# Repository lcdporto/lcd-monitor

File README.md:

# LCD Monitor

Project to create a Facilities Monitor and Access Control System  for a shared space.

As our work space is shared by several people, we want to have the greatest flexibility and at the same time security and responsibility, access control is a challenge that we have long tried to solve.

We resolved to cannibalize the current alarm and create a new one whose programming is much more flexible.

---

The progress of this project can be tracked (in Portuguese) in a [blog post](https://blog.lcdporto.org/project-lcd-monitor/) at our blog.

---

## Brief description

The console will be run by a Arduino and an API running on a server, the Arduino will handle all the sensors, keypad and buzzers independently.

The API (probably using Django REST) to communicate events and receive instructions.

After receiving new programming the API will pass it to the Arduino via  ethernet.

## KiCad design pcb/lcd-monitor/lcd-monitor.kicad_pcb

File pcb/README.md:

# LCD Monitor - PCB

## Requirements

* Pass 12v to the sensors and feed return signal throught optocouplers to the Arduino
* Signaling using LEDs (armed/clear/alarm/zones)
* PCB headers to the [keypad](16-Key-4-x-4-Membrane-Keypad.jpg)  
* PCB headers to hold Arduino Nano or, build an Arduino on the board
* Feed 5v to the Arduino
* PCB headers to [ethernet module](Mini-ENC28J60-Ethernet-LAN-Network-Module-AVR-SPI-PIC-STM32-LPC.jpg)
* Charging circuit to a 12v battery
* Anti-tampering push button on the board

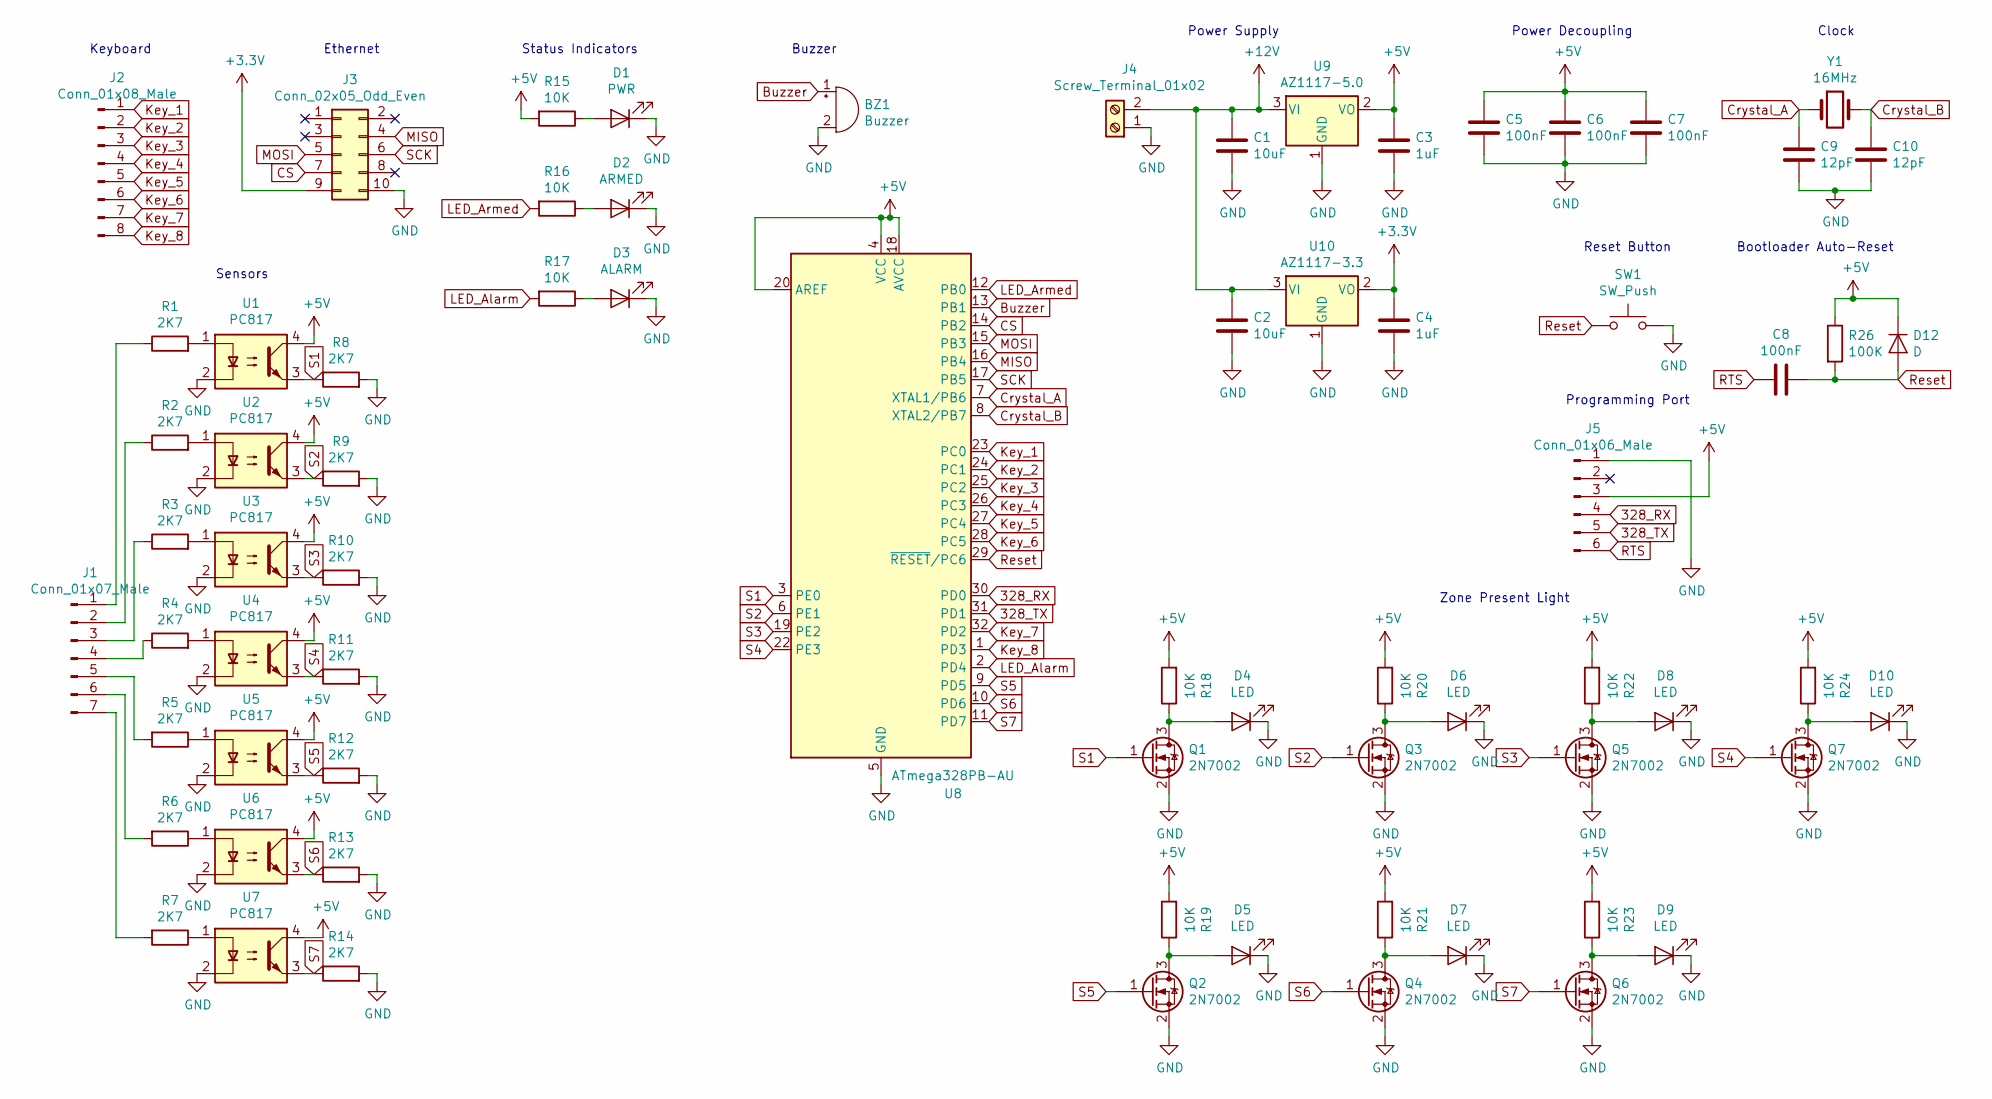
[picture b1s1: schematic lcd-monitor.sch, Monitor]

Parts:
BZ1: Buzzer; Buzzer_12x9.5RM7.6
C1, C2: 10uF; C_0805_2012Metric
C3, C4: 1uF; C_0805_2012Metric
C5, C6, C7, C8: 100nF; C_0805_2012Metric
C9, C10: 12pF; C_0805_2012Metric
D1: PWR; LED_0805_2012Metric
D2: ARMED; LED_0805_2012Metric
D3: ALARM; LED_0805_2012Metric
D4, D5, D6, D7, D8, D9, D10: LED; LED_0805_2012Metric
D12: D; D_0805_2012Metric
J1: Conn_01x07_Male; PinHeader_1x07_P2.54mm_Vertical
J2: Conn_01x08_Male; PinHeader_1x08_P2.54mm_Vertical
J3: Conn_02x05_Odd_Even; PinSocket_2x05_P2.54mm_Vertical
J4: Screw_Terminal_01x02; TerminalBlock_Altech_AK300-2_P5.00mm
J5: Conn_01x06_Male; PinHeader_1x06_P2.54mm_Vertical
Q1, Q2, Q3, Q4, Q5, Q6, Q7: 2N7002; SOT-23
R1, R2, R3, R4, R5, R6, R7, R8, R9, R10, R11, R12, R13, R14: 2K7; R_0805_2012Metric
R15, R16, R17, R18, R19, R20, R21, R22, R23, R24: 10K; R_0805_2012Metric
R26: 100K; R_0805_2012Metric
SW1: SW_Push; SW_SPST_FSMSM
U1, U2, U3, U4, U5, U6, U7: PC817; DIP-4_W7.62mm
U8: ATmega328PB-AU; TQFP-32_7x7mm_P0.8mm
U9: AZ1117-5.0; SOT-223
U10: AZ1117-3.3; SOT-223
Y1: 16MHz; Crystal_SMD_3225-4Pin_3.2x2.5mm

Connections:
328_RX: J5.4, U8.30 (PD0)
328_TX: J5.5, U8.31 (PD1)
+3V3: C4.1, J3.9, U10.2 (VO)
+5V: C3.1, C5.1, C6.1, C7.1, D12.1 (K), J5.3, R15.2, R18.2, R19.2, R20.2, R21.2, R22.2, R23.2, R24.2, R26.1, U1.4, U2.4, U3.4, U4.4, U5.4, U6.4, U7.4, U8.4 (VCC), U8.18 (AVCC), U8.20 (AREF), U9.2 (VO); also elsewhere on the board
+12V: C1.1, C2.1, J4.2, U9.3 (VI), U10.3 (VI)
Buzzer: BZ1.1 (-), U8.13 (PB1)
CS: J3.7, U8.14 (PB2)
Crystal_A: C9.1, U8.7 (XTAL1/PB6), Y1.1
Crystal_B: C10.1, U8.8 (XTAL2/PB7), Y1.2
GND: BZ1.2 (+), C1.2, C2.2, C3.2, C4.2, C5.2, C6.2, C7.2, C9.2, C10.2, D1.1 (K), D2.1 (K), D3.1 (K), D4.1 (K), D5.1 (K), D6.1 (K), D7.1 (K), D8.1 (K), D9.1 (K), D10.1 (K), J3.10, J4.1, J5.1, Q1.2 (S), Q2.2 (S), Q3.2 (S), Q4.2 (S), Q5.2 (S), Q6.2 (S), Q7.2 (S), R8.2, R9.2, R10.2, R11.2, R12.2, R13.2, R14.2, SW1.2, U1.2, U2.2, U3.2, U4.2, U5.2, U6.2, U7.2, U8.5 (GND), U8.21 (GND), U9.1 (GND), U10.1 (GND); also elsewhere on the board
Key_1: J2.1, U8.23 (PC0)
Key_2: J2.2, U8.24 (PC1)
Key_3: J2.3, U8.25 (PC2)
Key_4: J2.4, U8.26 (PC3)
Key_5: J2.5, U8.27 (PC4)
Key_6: J2.6, U8.28 (PC5)
Key_7: J2.7, U8.32 (PD2)
Key_8: J2.8, U8.1 (PD3)
LED_Alarm: R17.2, U8.2 (PD4)
LED_Armed: R16.2, U8.12 (PB0)
MISO: J3.4, U8.16 (PB4)
MOSI: J3.5, U8.15 (PB3)
unnamed: D1.2 (A), R15.1
unnamed: D2.2 (A), R16.1
unnamed: D3.2 (A), R17.1
unnamed: D4.2 (A), Q1.3 (D), R18.1
unnamed: D5.2 (A), Q2.3 (D), R19.1
unnamed: D6.2 (A), Q3.3 (D), R20.1
unnamed: D7.2 (A), Q4.3 (D), R21.1
unnamed: D8.2 (A), Q5.3 (D), R22.1
unnamed: D9.2 (A), Q6.3 (D), R23.1
unnamed: D10.2 (A), Q7.3 (D), R24.1
unnamed: J1.1, R1.1
unnamed: J1.2, R2.1
unnamed: J1.3, R3.1
unnamed: J1.4, R4.1
unnamed: J1.5, R5.2
unnamed: J1.6, R6.2
unnamed: J1.7, R7.2
unnamed: R1.2, U1.1
unnamed: R2.2, U2.1
unnamed: R3.2, U3.1
unnamed: R4.2, U4.1
unnamed: R5.1, U5.1
unnamed: R6.1, U6.1
unnamed: R7.1, U7.1
RTS: C8.2, J5.6
Reset: C8.1, D12.2 (A), R26.2, SW1.1, U8.29 (~RESET~/PC6)
S1: Q1.1 (G), R8.1, U1.3, U8.3 (PE0)
S3: Q5.1 (G), R10.1, U3.3, U8.19 (PE2)
S5: Q2.1 (G), R12.1, U5.3, U8.9 (PD5)
SCK: J3.6, U8.17 (PB5)

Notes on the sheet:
Clock
Power Decoupling
Bootloader Auto-Reset
Power Supply
Reset Button
Programming Port
Keyboard
Ethernet
Status Indicators
Buzzer
Sensors
Zone Present Light

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
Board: 2 copper layers, 74 parts (0 on the bottom side), 57 nets, no tracks yet.

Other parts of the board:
D11: LED; LED_0805_2012Metric
Q8: 2N7002; SOT-23
R25: 10K; R_0805_2012Metric

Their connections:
+5V: R25.2; also elsewhere on the board
GND: D11.1, Q8.2; also elsewhere on the board
unnamed: D11.2, Q8.3, R25.1

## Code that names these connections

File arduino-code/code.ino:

/*
 *
 *  Uses https://playground.arduino.cc/code/keypad
 *
 *
 */

#include "Arduino.h"
#include <EEPROM.h>
#include <Keypad.h>
#include <elapsedMillis.h>
#include "loadConfig.cpp"
/******************
 * PIN asignments
 */

// used by the keypad
byte rowPins[] = {A7,A6,A5,A4};
byte colPins[] = {A3,A2,A1,A0};

// active zones
const byte zones[2] = { 2, 3 };

// the LEDs
const byte LED_ALARM = 9;
const byte LED_ARMED = 13;

// the buzz
const byte Buzzer = 12;

// External alarm
const byte E_ALARM = 11;

/*
 * end PIN assigments
 *********************/


// struct with configuration to be stored on EEPROM
struct confSettings{
  bool zoneType[6];
  byte daferTime;
};

confSettings conf;

/* starting keypad */
// @TODO should this go into the function that andles the keypad
const char keys[4][4] = {
  {'1','2','3','A'},
  {'4','5','6','B'},
  {'7','8','9','C'},
  {'*','0','#','D'}
};
Keypad keypad = Keypad( makeKeymap(keys), rowPins, colPins, 4, 4 );

// Sound Codes
const byte sndStart=1;
const byte sndCancel=2;
const byte sndKeyPress=3;


/* zoneType: 0 = Instant Alarm; 1 = Deferred Alarm ); */
#define INSTANT_ALARM  1
#define DEFERRED_ALARM 0
bool zoneType[2] = {
  0,
  0
};

/* deferTime, time in seconds before a Deferred Alarm goes on */
byte deferTime = 15;

/* deferredAlarmState: 0 = no activity; 1 = in Deferred Alarm countdown */
bool deferredAlarmState = 0;
elapsedMillis deferredAlarmStart;

/* onAlarm: full blown Alarm in progress */
bool onAlarm = 0;
bool inInput=false;
bool isArmed=false;



int keyTone = 900;
int keyToneDuration = 50;
// =========================================================================88|

void setup() {

  // read EEPROM
  loadConfig();

  for ( int i = 0; i < sizeof(zones) - 1; i++ ) {
    pinMode(i,INPUT);
  }
  pinMode(LED_ALARM, OUTPUT); digitalWrite(LED_ALARM, HIGH);
  pinMode(LED_ARMED, OUTPUT); digitalWrite(LED_ARMED, HIGH);

  sound(sndStart);
  isArmed=true;
  Serial.begin(9600);
  delay(200);
}


/**
 * Da loop
 *
 * Faking multitasking, call all functions has fas as possible
 *
 */
void loop() {

  heartBeat();
  readZones();
  readKeypad();

  ledKeeper();
  soundKeeper();


}

// =========================================================================88|





//


/**
 * void hearBeat()
 *
 * give visual feedback that the software is running by temporarely inverting
 * the status of LED_ARMED
 */
#define HEART_BEAT_SLEEP 1000
#define HEART_BEAT_DURATION 50  // must be lower than HEART_BEAT_SLEEP
void heartBeat()
{
  static elapsedMillis timeElapsed;
  static bool onBeat = false; // if a heartbeat is currently ocorring

  if ( ( onBeat && timeElapsed > HEART_BEAT_DURATION ) || ( timeElapsed > HEART_BEAT_SLEEP ) )
  {
    onBeat = !onBeat;
    digitalWrite( LED_ARMED, !digitalRead( LED_ARMED ) );
    timeElapsed = 0;
  }

}


/* Read All Zones and trigger Alarm Events */
void readZones() {
  for ( int zone = 0; zone < sizeof(zones); zone++ ) {

    if( ( !digitalRead(zones[zone]) ) && isArmed ) {

      if ( zoneType[zone] = INSTANT_ALARM ) {
        onAlarm=true;
      } else {
        deferredAlarmState=true;
        deferredAlarmStart = 0;
      }

    }
  }

  // Serial.print("deferredAlarmState: ");
  // Serial.println(deferredAlarmState);
  if (
    deferredAlarmState &&
    ( deferredAlarmStart >  deferTime ) &&
    ( ! onAlarm )
  ) {
    onAlarm=true;
  }
}


/* Read the Keypad and trigger avents */
void readKeypad() {
  const byte IdleTimeBetweenKeyPresses = 10;
  static String inputString = "";
  static unsigned long lastKeypress;

  char key = keypad.getKey();

  if (key != NO_KEY){
    lastKeypress = millis();
    sound(sndKeyPress);
    inputString += key;
    if(key == 'A') {
    }
    if(key == '#') inputString = "";
  }


/*
  // if idle time passes cancel input state
  if ( (long)( millis() - lastKeypress )  <
       (long)( IdleTimeBetweenKeyPresses * 1000 ) ) {
    inputString = "";
    inInput = false;
    // sound(sndCancel);
  }
*/
}

void ledKeeper() {
  /*
  digitalWrite(LED_ARMED,isArmed);
  digitalWrite(LED_ALARM,onAlarm);
  */
}

void sound(byte sndCode) {
  tone(Buzzer,500,100);
}

void soundKeeper() {
  #define kks 500
}

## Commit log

2018-10-09 adds requirements
2018-10-12 adds README.md
2018-10-16 api: Criar pasta e README
    Actualizar os requisitos principais com uma referência para os de cada
    componente.
2018-10-16 Rename requimes to requirements.
2018-10-16 Updates project description - remove mention to Rapsberry PI
2018-10-16 adds basic requirements for the PCB
2018-10-18 PCB Schematic Alpha Version
2018-10-18 Buzzer through PWM
2018-10-19 Fix Optocoupler Resistor Values
2018-10-19 Assign Footprints
2018-10-19 Fix Ethernet Header
2018-10-19 Assign footprint for the new Ethernet header
2018-10-19 Remove unused CTS signal
2018-10-19 PCB first desing (not working)
2018-10-24 adds first tests to arduino code
2018-11-03 Add zone status led
2018-11-03 Fix status LEDs
2019-02-26 starts arduinio coding....
2019-02-26 adds an example of usage of the EtherCard library
2019-02-27 Translate to PlatformIO
2019-02-28 resolves compile errors after migration to platformIO
2019-03-04 WIP: starts class 'configuration'
2019-03-05 adds conf of mac address
2019-03-05 Set Anti-Tampering Pin
2019-03-05 Password Storage and Authentication
2019-03-05 Moved initial alarm password to a define statement
2019-03-05 store stuff
2019-03-06 Added debug serial prints and EEPROM password add, remove and update.
2019-03-06 removes test function 'sherwood'
2019-03-06 implements use of EEPROM_PASSWORD_BEGIN_ADDRESS
2019-03-06 adds configuration for zones and adapts main for usage
2019-03-06 api: Initial DjangoREST code.
2019-03-06 api: Actualizar README
2019-03-06 api: Activar REST-Framework no django
2019-03-13 Ethernet Initialized
